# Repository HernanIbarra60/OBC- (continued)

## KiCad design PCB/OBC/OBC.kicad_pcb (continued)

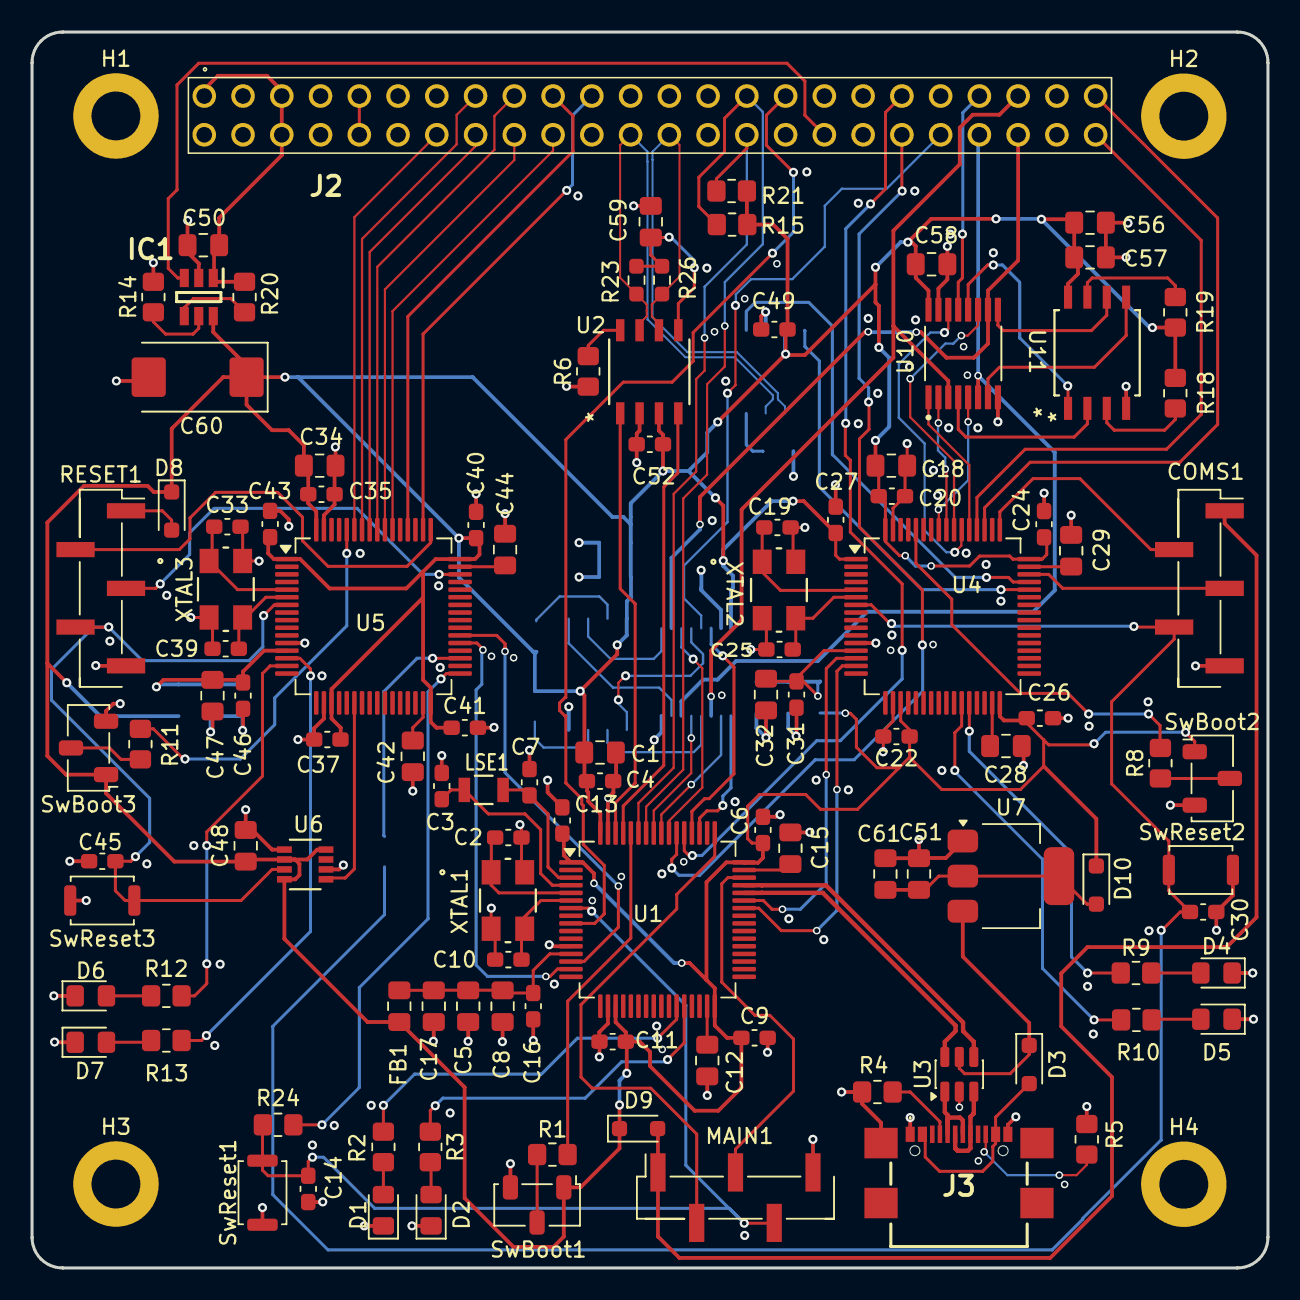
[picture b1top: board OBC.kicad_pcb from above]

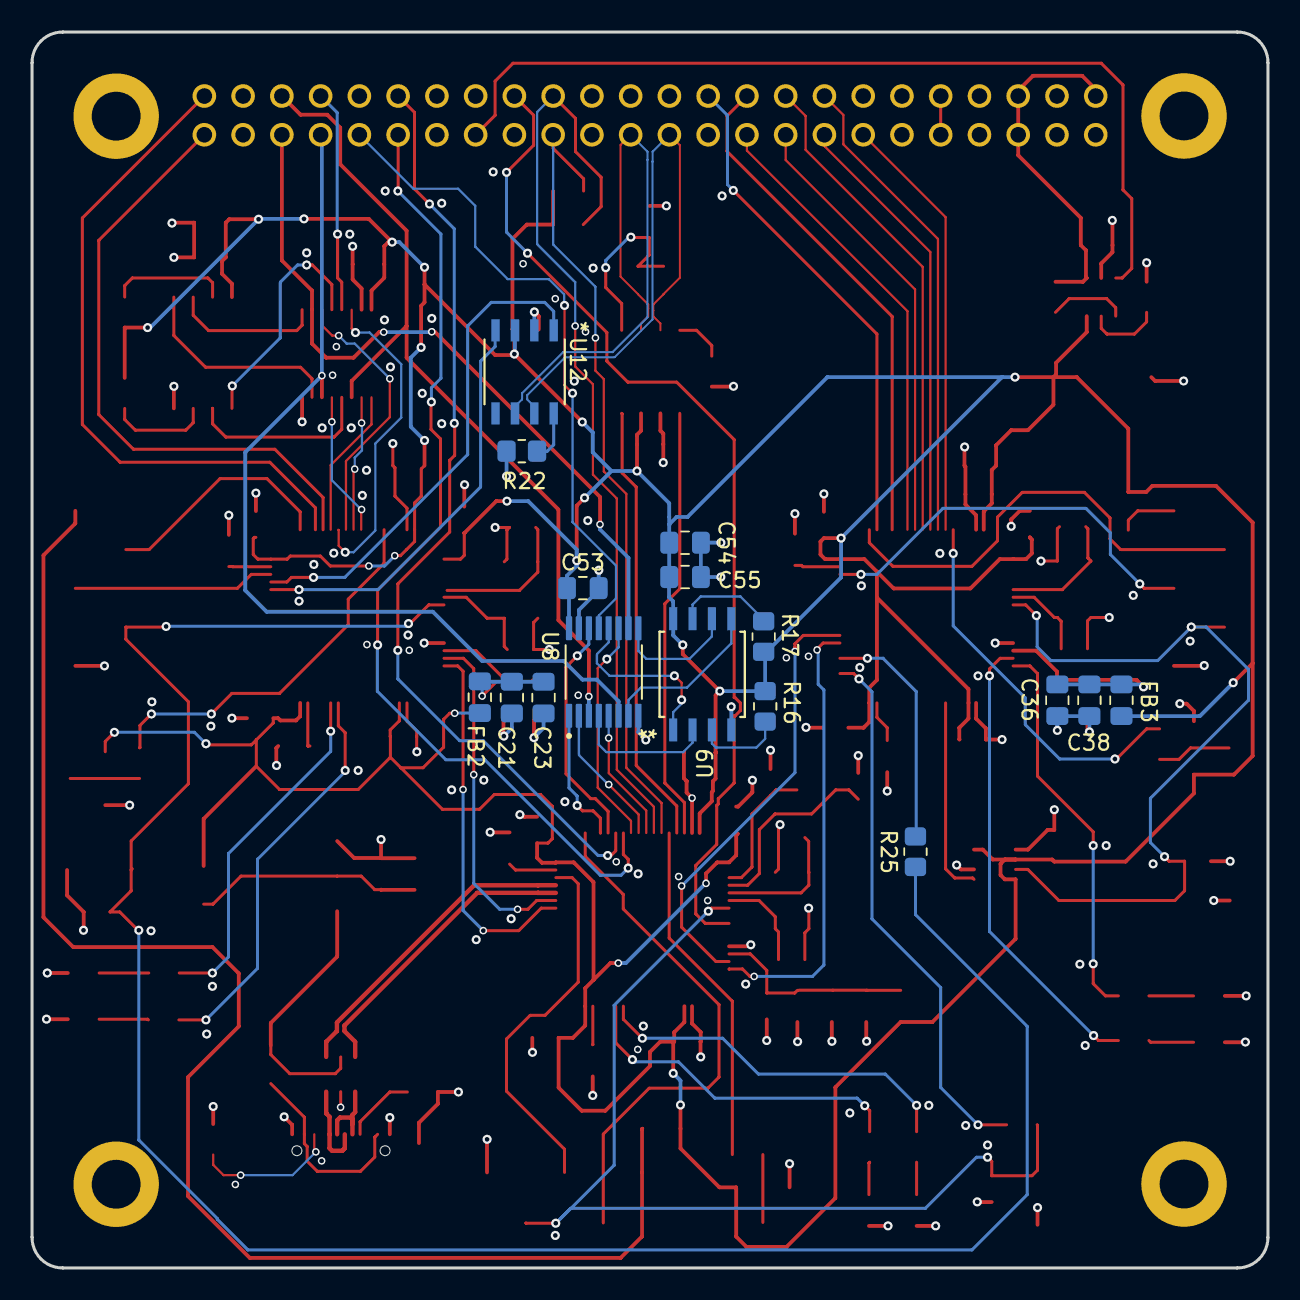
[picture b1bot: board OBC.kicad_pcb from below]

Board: 4 copper layers, 81.0 x 81.0 mm, 131 parts (16 on the bottom side), 120 nets.

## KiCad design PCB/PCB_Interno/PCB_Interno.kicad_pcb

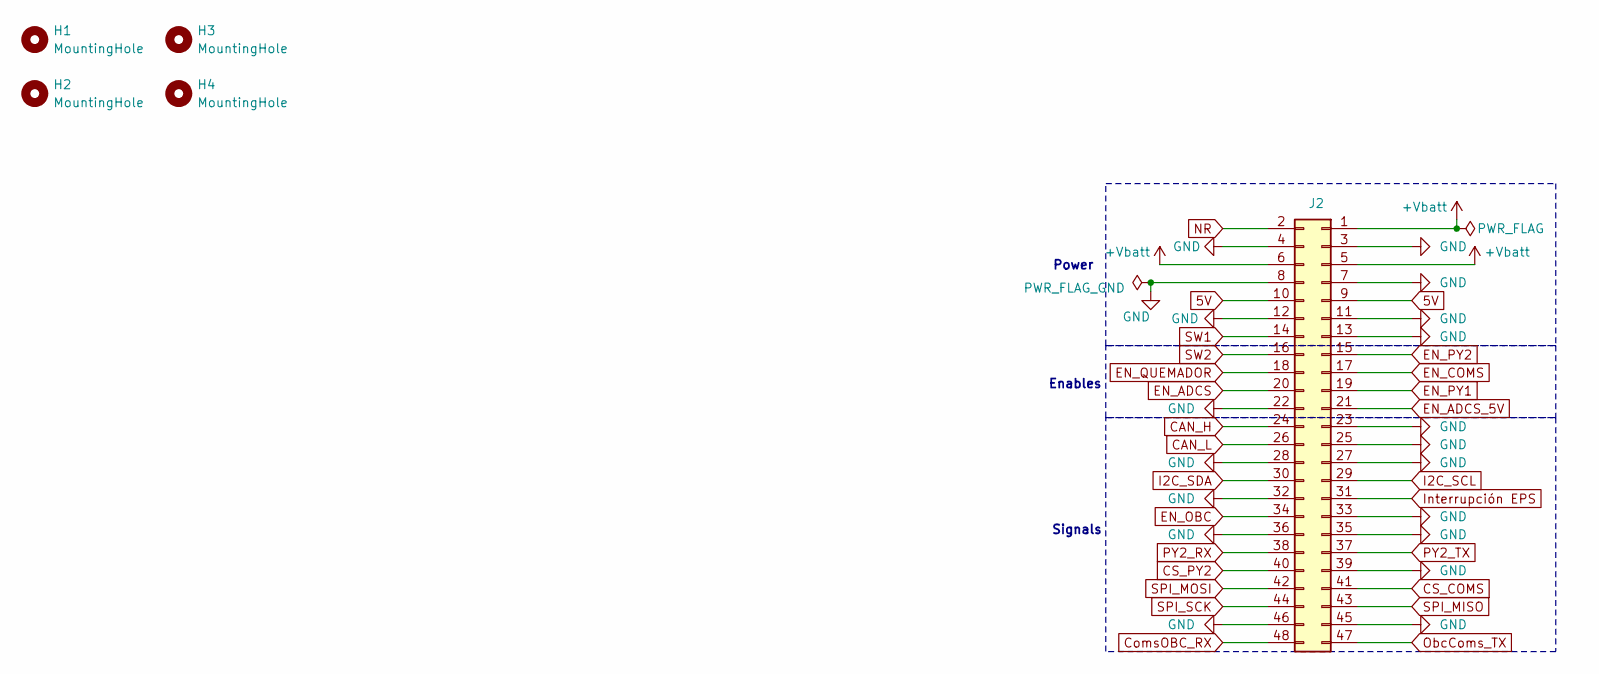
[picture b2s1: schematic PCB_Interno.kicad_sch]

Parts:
H1, H2, H3, H4: MountingHole; MountingHole_3.2mm_M3_DIN965_Pad
J2: Conn_02x24_Odd_Even; ESQ-124-Y-X-D

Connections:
5V: J2.9, J2.10
+Vbatt: J2.1, J2.5, J2.6
CAN_H: J2.24
CAN_L: J2.26
CS_COMS: J2.41
CS_PY2: J2.40
ComsOBC_RX: J2.48
EN_ADCS: J2.20
EN_ADCS_5V: J2.21
EN_COMS: J2.17
EN_OBC: J2.34
EN_PY1: J2.19
EN_PY2: J2.15
EN_QUEMADOR: J2.18
GND: J2.3, J2.4, J2.7, J2.8, J2.11, J2.12, J2.13, J2.22, J2.23, J2.25, J2.27, J2.28, J2.32, J2.33, J2.35, J2.36, J2.39, J2.45, J2.46
I2C_SCL: J2.29
I2C_SDA: J2.30
Interrupción EPS: J2.31
NR: J2.2
ObcComs_TX: J2.47
PY2_RX: J2.38
PY2_TX: J2.37
SPI_MISO: J2.43
SPI_MOSI: J2.42
SPI_SCK: J2.44
SW1: J2.14
SW2: J2.16

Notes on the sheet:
Power
Enables
Signals

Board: 2 copper layers, 5 parts (0 on the bottom side), 3 nets, no tracks yet.

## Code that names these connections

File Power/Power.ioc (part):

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Mcu.Name=STM32F405RGTx
Mcu.Package=LQFP64
Mcu.UserName=STM32F405RGTx
PA0-WKUP.GPIOParameters=GPIO_Label
PA0-WKUP.GPIO_Label=ledGreen
PA0-WKUP.Signal=GPIO_Output
PA1.GPIOParameters=GPIO_Label
PA1.GPIO_Label=ledRed
PA1.Signal=GPIO_Output
PA13.Mode=Serial_Wire
PA13.Signal=SYS_JTMS-SWDIO
PA14.Mode=Serial_Wire
PA14.Signal=SYS_JTCK-SWCLK
PA15.GPIOParameters=GPIO_Label
PA15.GPIO_Label=EN_ADCS_5V
PA15.Signal=GPIO_Output
PA6.GPIOParameters=GPIO_Label
PA6.GPIO_Label=watchdog
PA6.Signal=GPIO_Output
PB1.GPIOParameters=GPIO_Label
PB1.GPIO_Label=LedG
PB1.Signal=GPIO_Output
PB12.GPIOParameters=PinState,GPIO_PuPd,GPIO_Label,GPIO_ModeDefaultOutputPP
PB12.GPIO_Label=MainRst
PB12.GPIO_ModeDefaultOutputPP=GPIO_MODE_OUTPUT_OD
PB12.GPIO_PuPd=GPIO_NOPULL
PB12.PinState=GPIO_PIN_SET
PB12.Signal=GPIO_Output
PB14.GPIOParameters=PinState,GPIO_PuPd,GPIO_Label,GPIO_ModeDefaultOutputPP
PB14.GPIO_Label=ComsRst
PB14.GPIO_ModeDefaultOutputPP=GPIO_MODE_OUTPUT_OD
PB14.GPIO_PuPd=GPIO_NOPULL
PB14.PinState=GPIO_PIN_SET
PB14.Signal=GPIO_Output
PB2.GPIOParameters=GPIO_Label
PB2.GPIO_Label=LedR
PB2.Signal=GPIO_Output
PB3.GPIOParameters=GPIO_Label
PB3.GPIO_Label=EN_QUEMADOR
PB3.Signal=GPIO_Output
PB4.GPIOParameters=GPIO_Label
PB4.GPIO_Label=EN_COMS
PB4.Signal=GPIO_Output
PB5.GPIOParameters=GPIO_Label
PB5.GPIO_Label=SW2
PB5.Signal=GPIO_Input
PB6.GPIOParameters=GPIO_Label
PB6.GPIO_Label=EN_PY2
PB6.Signal=GPIO_Output
PB7.GPIOParameters=GPIO_Label
PB7.GPIO_Label=SW1
PB7.Signal=GPIO_Input
PC11.GPIOParameters=GPIO_Label
PC11.GPIO_Label=EN_PY1
PC11.Signal=GPIO_Output
PC14-OSC32_IN.Mode=LSE-External-Oscillator
PC14-OSC32_IN.Signal=RCC_OSC32_IN
PC15-OSC32_OUT.Mode=LSE-External-Oscillator
PC15-OSC32_OUT.Signal=RCC_OSC32_OUT
PC6.GPIOParameters=GPIO_Label
PC6.GPIO_Label=MainPwr_RX
PC6.Mode=Asynchronous
PC6.Signal=USART6_TX
PC7.GPIOParameters=GPIO_Label
PC7.GPIO_Label=MainPwr_TX
PC7.Mode=Asynchronous
PC7.Signal=USART6_RX
PD2.GPIOParameters=GPIO_Label
PD2.GPIO_Label=EN_ADCS
PD2.Signal=GPIO_Output
PH0-OSC_IN.Mode=HSE-External-Oscillator
PH0-OSC_IN.Signal=RCC_OSC_IN
PH1-OSC_OUT.Mode=HSE-External-Oscillator
PH1-OSC_OUT.Signal=RCC_OSC_OUT
RCC.HSE_VALUE=25000000
RCC.SYSCLKFreq_VALUE=16000000
board=custom

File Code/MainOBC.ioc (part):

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Mcu.Name=STM32F405RGTx
Mcu.Package=LQFP64
Mcu.UserName=STM32F405RGTx
PA0-WKUP.GPIOParameters=GPIO_Label
PA0-WKUP.GPIO_Label=MainPwr_TX
PA0-WKUP.Mode=Asynchronous
PA0-WKUP.Signal=UART4_TX
PA1.GPIOParameters=GPIO_Label
PA1.GPIO_Label=MainPwr_RX
PA1.Mode=Asynchronous
PA1.Signal=UART4_RX
PA10.GPIOParameters=GPIO_Label
PA10.GPIO_Label=Coms_rx
PA10.Mode=Asynchronous
PA10.Signal=USART1_RX
PA11.Mode=Device_Only
PA11.Signal=USB_OTG_FS_DM
PA12.Mode=Device_Only
PA12.Signal=USB_OTG_FS_DP
PA13.Mode=Serial_Wire
PA13.Signal=SYS_JTMS-SWDIO
PA14.Mode=Serial_Wire
PA14.Signal=SYS_JTCK-SWCLK
PA2.Mode=Asynchronous
PA2.Signal=USART2_TX
PA3.Mode=Asynchronous
PA3.Signal=USART2_RX
PA4.Mode=NSS_Signal_Hard_Output
PA4.Signal=SPI1_NSS
PA5.Mode=Full_Duplex_Master
PA5.Signal=SPI1_SCK
PA6.Mode=Full_Duplex_Master
PA6.Signal=SPI1_MISO
PA7.Mode=Full_Duplex_Master
PA7.Signal=SPI1_MOSI
PA9.GPIOParameters=GPIO_Label
PA9.GPIO_Label=coms_tx
PA9.Mode=Asynchronous
PA9.Signal=USART1_TX
PB3.Mode=Full_Duplex_Master
PB3.Signal=SPI3_SCK
PB4.Mode=Full_Duplex_Master
PB4.Signal=SPI3_MISO
PB5.Mode=Full_Duplex_Master
PB5.Signal=SPI3_MOSI
PB6.Mode=I2C
PB6.Signal=I2C1_SCL
PB7.Mode=I2C
PB7.Signal=I2C1_SDA
PB8.Mode=CAN_Activate
PB8.Signal=CAN1_RX
PB9.Mode=CAN_Activate
PB9.Signal=CAN1_TX
PC1.GPIOParameters=GPIO_Label
PC1.GPIO_Label=Interrupcion EPS
PC1.Signal=GPXTI1
PC10.GPIOParameters=GPIO_Label
PC10.GPIO_Label=EnMuxPy
PC10.Signal=GPIO_Output
PC11.GPIOParameters=GPIO_Label
PC11.GPIO_Label=CsMemPy
PC11.Signal=GPIO_Output
PC12.GPIOParameters=GPIO_Label
PC12.GPIO_Label=PY2_TX
PC12.Mode=Asynchronous
PC12.Signal=UART5_TX
PC13-ANTI_TAMP.Signal=GPXTI13
PD2.GPIOParameters=GPIO_Label
PD2.GPIO_Label=PY2_RX
PD2.Mode=Asynchronous
PD2.Signal=UART5_RX
PH0-OSC_IN.Mode=HSE-External-Oscillator
PH0-OSC_IN.Signal=RCC_OSC_IN
PH1-OSC_OUT.Mode=HSE-External-Oscillator
PH1-OSC_OUT.Signal=RCC_OSC_OUT
RCC.HSE_VALUE=8000000
RCC.SYSCLKFreq_VALUE=168000000
RCC.SYSCLKSource=RCC_SYSCLKSOURCE_PLLCLK
board=custom
